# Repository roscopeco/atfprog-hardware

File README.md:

## ATF150x programmer (commercial)

Made non-proprietary and released to open-source with the
licenses outlined in LICENSE.md and LICENSE.hardware, 
under my authority on April 23rd 2025.

_Ross Bamford_

_Managing Director_

_The Really Old-School Company Limited_

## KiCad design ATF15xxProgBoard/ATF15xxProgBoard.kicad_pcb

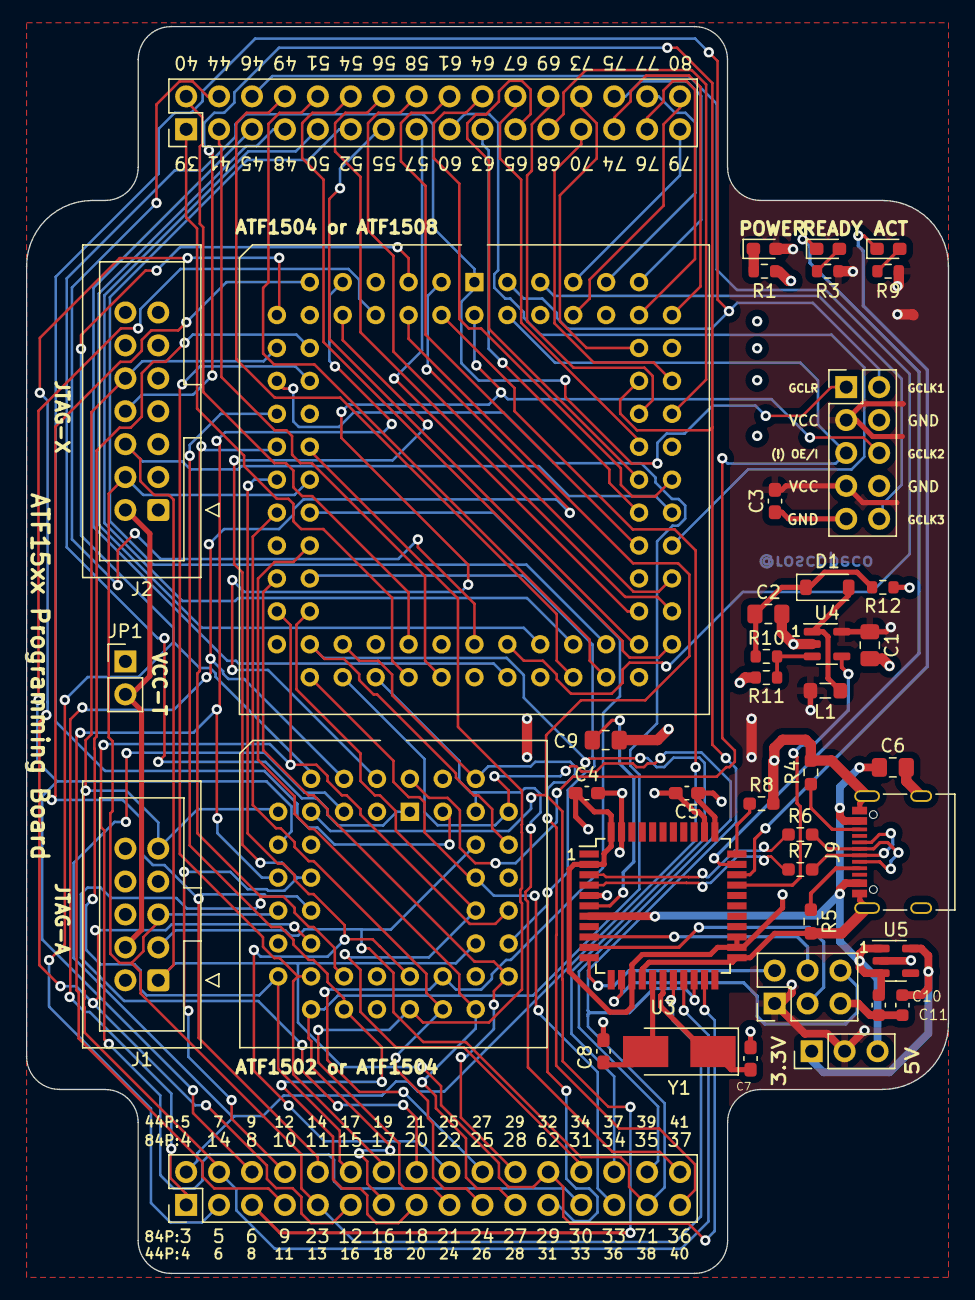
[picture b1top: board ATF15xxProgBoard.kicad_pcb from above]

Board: 4 copper layers, 71.1 x 96.2 mm, 42 parts (0 on the bottom side), 97 nets.

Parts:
C1, C2, C6: 10u; C_0805_2012Metric_Pad1.18x1.45mm_HandSolder
C3, C4, C5: 100n; C_0603_1608Metric_Pad1.08x0.95mm_HandSolder
C7, C8: 22p; C_0603_1608Metric_Pad1.08x0.95mm_HandSolder
C9: 1u; C_0805_2012Metric_Pad1.18x1.45mm_HandSolder
C10, C11: 4.7u; C_0603_1608Metric
D1: 1N4148; D_SOD-123
J1: Conn_02x05_Odd_Even; IDC-Header_2x05_P2.54mm_Vertical
J2: Conn_02x07_Odd_Even; IDC-Header_2x07_P2.54mm_Vertical
J6, J7: Conn_02x16_Counter_Clockwise; PinHeader_2x16_P2.54mm_Vertical
J8: Conn_02x03_Odd_Even; PinHeader_2x05_P2.54mm_Vertical
J9: USB_C; USB_C_Receptacle_Palconn_UTC16-G
J10: Conn_02x03_Odd_Even; PinHeader_2x03_P2.54mm_Vertical
JP1: Jumper_2_Bridged; PinHeader_1x02_P2.54mm_Vertical
JP2: Voltage; PinHeader_1x03_P2.54mm_Vertical
L1: 4.7uH; L_0805_2012Metric_Pad1.05x1.20mm_HandSolder
LED1: RED; LED_0603_1608Metric_Pad1.05x0.95mm_HandSolder
LED2: GREEN; LED_0603_1608Metric_Pad1.05x0.95mm_HandSolder
LED3: ORANGE; LED_0603_1608Metric_Pad1.05x0.95mm_HandSolder
R1, R3, R9: 2K; R_0603_1608Metric
R4, R5: 5.1K; R_0603_1608Metric_Pad0.98x0.95mm_HandSolder
R6, R7: 22R; R_0603_1608Metric_Pad0.98x0.95mm_HandSolder
R8: 10k; R_0603_1608Metric_Pad0.98x0.95mm_HandSolder
R10: 100K; R_0603_1608Metric
R11: 10K; R_0603_1608Metric
R12: 2.2K; R_0603_1608Metric
U1: PLCC-44_THT-Socket
U2: PLCC-84_THT-Socket
U3: ATmega32U4-AU; TQFP-44_10x10mm_P0.8mm
U4: MT3540; SOT-23-5
U5: AP2127K-3.3; SOT-23-5
Y1: 8MHz; Crystal_SMD_5032-2Pin_5.0x3.2mm_HandSoldering

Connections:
+3V3: C11.1, JP2.1 (A), U5.5 (VOUT)
/32_XTAL1: C7.1, U3.17 (XTAL1), Y1.1
/IO1: J6.1, U1.4 (I/O), U2.3 (I/O)
/IO2: J6.2, U1.5 (I/O), U2.4 (I/O)
/IO3: J6.3, U1.6 (I/O), U2.5 (I/O)
/IO5: J6.5, U1.8 (I/O), U2.6 (I/O)
/IO6: J6.6, U1.9 (I/O), U2.8 (I/O)
/IO7: J6.7, U1.11 (PD1/I/O), U2.9 (I/O)
/IO8: J6.8, U1.12 (I/O), U2.10 (I/O)
/IO10: J6.10, U1.14 (I/O), U2.11 (I/O)
/IO11: J6.11, U1.16 (I/O), U2.12 (I/O)
/IO12: J6.12, U1.17 (I/O), U2.15 (I/O)
/IO13: J6.13, U1.18 (I/O), U2.16 (I/O)
/IO14: J6.14, U1.19 (I/O), U2.17 (I/O)
/IO15: J6.15, U1.20 (I/O), U2.18 (I/O)
/IO16: J6.16, U1.21 (I/O), U2.20 (PD1/I/O)
/IO17: J6.17, U1.24 (I/O), U2.21 (I/O)
/IO18: J6.18, U1.25 (PD2/I/O), U2.22 (I/O)
/IO19: J6.19, U1.26 (I/O), U2.24 (I/O)
/IO20: J6.20, U1.27 (I/O), U2.25 (I/O)
/IO21: J6.21, U1.28 (I/O), U2.27 (I/O)
/IO22: J6.22, U1.29 (I/O), U2.28 (I/O)
/IO23: J6.23, U1.31 (I/O), U2.29 (I/O)
/IO25: J6.25, U1.33 (I/O), U2.30 (I/O)
/IO26: J6.26, U1.34 (I/O), U2.31 (I/O)
/IO27: J6.27, U1.36 (I/O), U2.33 (I/O)
/IO28: J6.28, U1.37 (I/O), U2.34 (I/O)
/IO30: J6.30, U1.39 (I/O), U2.35 (I/O)
/IO31: J6.31, U1.40 (I/O), U2.36 (I/O)
/IO32: J6.32, U1.41 (GCLK3/I/O), U2.37 (I/O)
/IO33: J7.1, U2.39 (I/O)
/IO34: J7.2, U2.40 (I/O)
/IO35: J7.3, U2.41 (I/O)
/IO36: J7.4, U2.44 (I/O)
/IO37: J7.5, U2.45 (I/O)
/IO38: J7.6, U2.46 (I/O/PD2)
/IO39: J7.7, U2.48 (I/O)
/IO40: J7.8, U2.49 (I/O)
/IO41: J7.9, U2.50 (I/O)
/IO42: J7.10, U2.51 (I/O)
/IO43: J7.11, U2.52 (I/O)
/IO44: J7.12, U2.54 (I/O)
/IO45: J7.13, U2.55 (I/O)
/IO46: J7.14, U2.56 (I/O)
/IO47: J7.15, U2.57 (I/O)
/IO48: J7.16, U2.58 (I/O)
/IO49: J7.17, U2.60 (I/O)
/IO50: J7.18, U2.61 (I/O)
/IO52: J7.19, U2.63 (I/O)
/IO53: J7.20, U2.64 (I/O)
/IO54: J7.21, U2.65 (I/O)
/IO55: J7.22, U2.67 (I/O)
/IO56: J7.23, U2.68 (I/O)
/IO57: J7.24, U2.69 (I/O)
/IO58: J7.25, U2.70 (I/O)
/IO60: J7.26, U2.73 (I/O)
/IO61: J7.27, U2.74 (I/O)
/IO62: J7.28, U2.75 (I/O)
/IO63: J7.29, U2.76 (I/O)
/IO64: J7.30, U2.77 (I/O)
/IO65: J7.31, U2.79 (I/O)
/IO66: J7.32, U2.80 (I/O)
/PDI: J10.3, U3.10 (PB2)
/PDO: J10.2, U3.11 (PB3)
/SCLK: J10.4, U3.9 (PB1)
/USBD+: R7.1, U3.4 (D+)
/USBD-: R6.1, U3.3 (D-)
/VPP_EN: U3.30 (PB6), U4.4 (EN)
/~ACT: LED3.1 (K), U3.31 (PC6)
/~RDY: LED2.1 (K), U3.32 (PC7)
/~RESET: J10.6, U3.13 (~RESET)
GCL2/I: J8.6, U1.2 (GCL2/OE2/I), U2.2 (GCLK2/OE2/I)
GCLK1/I: J8.2, U1.43 (GCLK1/I), U2.83 (GCLK1/I)
GCLK3/IO: J8.10, U2.81 (GCLK3/I/O)
GCLR/I: J8.1, U1.1 (GCLR/I), U2.1 (GCLR/I)
GND: C1.2, C2.2, C3.1, C4.2, C5.2, C6.2, C7.2, C8.2, C9.2, C10.2, C11.2, J1.2, J1.10, J2.1, J2.3, J2.5, J2.7, J2.9, J2.11, J2.13, J8.4, J8.8, J8.9, J9.A1 (GND), J9.A12 (GND), J9.B1 (GND), J9.B12 (GND), J9.S1 (SHIELD), J10.5, R1.2, R4.2, R5.2, R8.1, R11.2, U1.10 (GND), U1.22 (GND), U1.30 (GND), U1.42 (GND), U2.7 (GND), U2.19 (GND), U2.32 (GND), U2.42 (GND), U2.47 (GND), U2.59 (GND), U2.72 (GND), U2.82 (GND), U3.5 (UGND), U3.15 (GND), U3.23 (GND), U3.35 (GND), U3.43 (GND), U4.2 (GND), U5.2 (GND)
unnamed: D1.2 (A), L1.2, U4.1 (SW)
unnamed: C2.1, D1.1 (K), R10.1, R12.2
unnamed: J1.4, J2.2, JP1.2 (B)
unnamed: J9.A5 (CC1), R5.1
unnamed: J9.B5 (CC2), R4.1
unnamed: J9.A6 (D+), J9.B6 (D+), R7.2
unnamed: J9.A7 (D-), J9.B7 (D-), R6.2
unnamed: LED1.1 (K), R1.1
unnamed: LED2.2 (A), R3.2
unnamed: LED3.2 (A), R9.2
unnamed: C9.1, U3.6 (UCAP)
unnamed: C8.1, U3.16 (XTAL2), Y1.2
unnamed: R8.2, U3.33 (~HWB/PE2)
unnamed: R10.2, R11.1, U4.3 (FB)
OE1/I: J8.5, R12.1, U1.44 (OE1/I), U2.84 (OE1/I)
TCK: J1.1, J2.6, J6.24, U1.32 (I/O/TCK), U2.62 (TCK/I/O), U3.21 (PD3)
TDI: J1.9, J2.10, J6.4, U1.7 (TDI/I/O), U2.14 (TDI/I/O), U3.19 (PD1)
TDO: J1.3, J2.8, J6.29, U1.38 (I/O/TDO), U2.71 (TDO/I/O), U3.20 (PD2)
TMS: J1.5, J2.4, J6.9, U1.13 (I/O/TMS), U2.23 (TMS/I/O), U3.18 (PD0)
VBUS: C6.1, C10.1, J9.A4 (VBUS), J9.A9 (VBUS), J9.B4 (VBUS), J9.B9 (VBUS), JP2.3 (B), U3.7 (VBUS), U5.1 (VIN), U5.3 (EN)
VCC: C1.1, C3.2, C4.1, C5.1, J8.3, J8.7, J10.1, JP1.1 (A), JP2.2 (C), L1.1, LED1.2 (A), R3.1, R9.1, U1.3 (VCC), U1.15 (VCC), U1.23 (VCC), U1.35 (VCC), U2.13 (VCCIO), U2.26 (VCCIO), U2.38 (VCCIO), U2.43 (VCCINT), U2.53 (VCCIO), U2.66 (VCCIO), U2.78 (VCCIO), U3.2 (UVCC), U3.14 (VCC), U3.24 (AVCC), U3.25 (PD4), U3.34 (VCC), U3.44 (AVCC), U4.5 (IN)

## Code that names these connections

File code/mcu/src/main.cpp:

#include <PlayXSVFJTAGArduino.h>
//#include <PlayXSVFJTAGAVR.h>

//
// The maximum size of the arduino receive buffer is 63 bytes by default.
// This number can be changed if you change the compiler flags in the
// file hardware/arduino/avr/platform.local.txt (-O2 makes it faster):
//
// compiler.c.extra_flags=-DSERIAL_BUFFER_SIZE=256 -DSERIAL_RX_BUFFER_SIZE=256 -O2
// compiler.cpp.extra_flags=-DSERIAL_BUFFER_SIZE=256 -DSERIAL_RX_BUFFER_SIZE=256 -O2
//

#define VERSION		"1.01"

#ifndef SERIAL_RX_BUFFER_SIZE
#define SERIAL_RX_BUFFER_SIZE 64
#endif /* SERIAL_RX_BUFFER_SIZE */

#ifdef ARDUINO_MEGA
#error Building for Arduino not currently supported
#define TMS_PIN  	8
#define TDI_PIN  	9
#define TDO_PIN  	10
#define TCK_PIN  	11
#define VREF_PIN 	12
#else
#define VPP_EN		8	// PB6
#define ACT_LED		5	// PC6
#define RDY_LED		6	// PC7
#define TMS_PIN  	19	// PD0
#define TDI_PIN  	18	// PD1
#define TDO_PIN  	0	// PD2
#define TCK_PIN  	1	// PD3
#define VREF_PIN 	12	// Should be PD4...
#endif

void setup()
{
	pinMode(VPP_EN, OUTPUT);
	pinMode(ACT_LED, OUTPUT);
	pinMode(RDY_LED, OUTPUT);

	digitalWrite(VPP_EN, LOW);
	digitalWrite(ACT_LED, LOW);
	digitalWrite(RDY_LED, LOW);

	Serial.begin(115200);

	digitalWrite(RDY_LED, HIGH);

	// Wait for USB serial...
	bool act_on = true;
	while (!Serial) {
		for (int i = 0; i < 10; i++) {
			if (Serial) {
				break;
			} else {
				delay(100);
			}
		}

		// 1sec
		act_on = !act_on;
		digitalWrite(ACT_LED, act_on ? LOW : HIGH);
	}

	digitalWrite(ACT_LED, HIGH);
	digitalWrite(RDY_LED, LOW);
}

void loop()
{
	digitalWrite(VPP_EN, LOW);

	while (true) {
		int command = Serial.read();

		if (command == 'G') {
			// Go - break to play
			break;
		}
		if (command == 'H') {
			// High voltage go - enable and break to play
			digitalWrite(VPP_EN, HIGH);
			break;
		}
		if (command == 'V') {
			// Dump version
			Serial.print(F("\r\nQ0,"));
			Serial.print("Little ATF Programmer Board v");
			Serial.println(VERSION);
		}
	}

	PlayXSVFJTAGArduino p(Serial, SERIAL_RX_BUFFER_SIZE, TMS_PIN, TDI_PIN, TDO_PIN, TCK_PIN, VREF_PIN, true);
	//PlayXSVFJTAGAVR p(Serial, SERIAL_RX_BUFFER_SIZE);

	p.play();	
}

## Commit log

2024-04-12 COMMERCIAL: Full redesign as programmer
2024-04-25 Minor tidy up
2024-04-25 Ignore .DS_Store
2024-04-25 Functionality for programmer board
2024-05-21 Add docs
2025-07-12 Open sourcing

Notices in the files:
ATF15xxProgBoard/ATF15xxProgBoard.kicad_pcb:
Copyright ©2024
